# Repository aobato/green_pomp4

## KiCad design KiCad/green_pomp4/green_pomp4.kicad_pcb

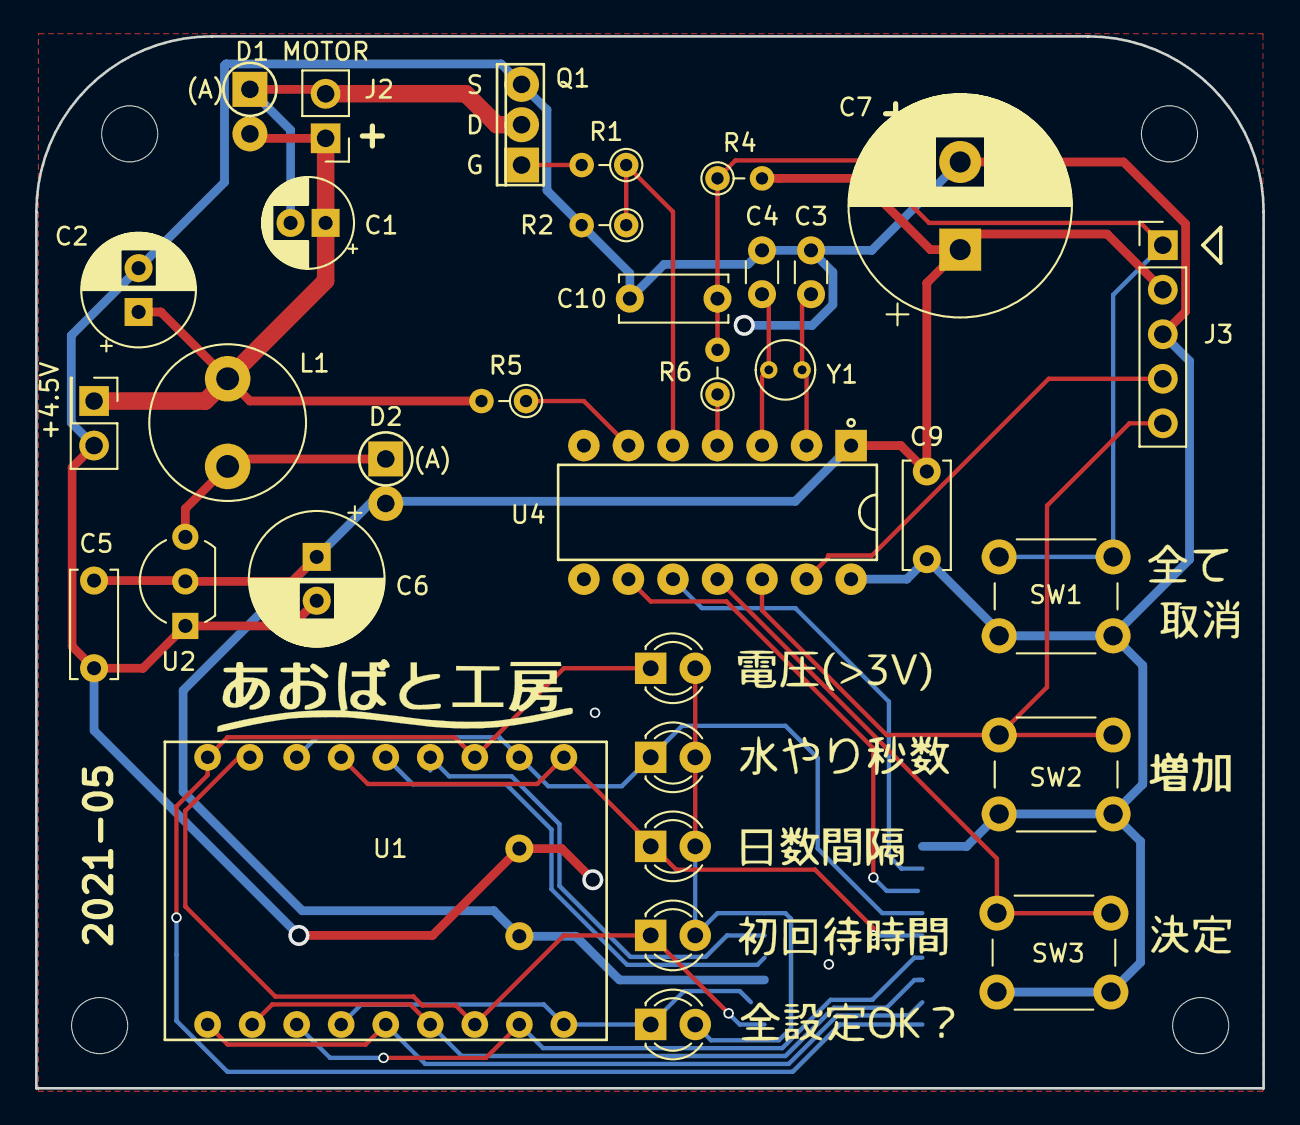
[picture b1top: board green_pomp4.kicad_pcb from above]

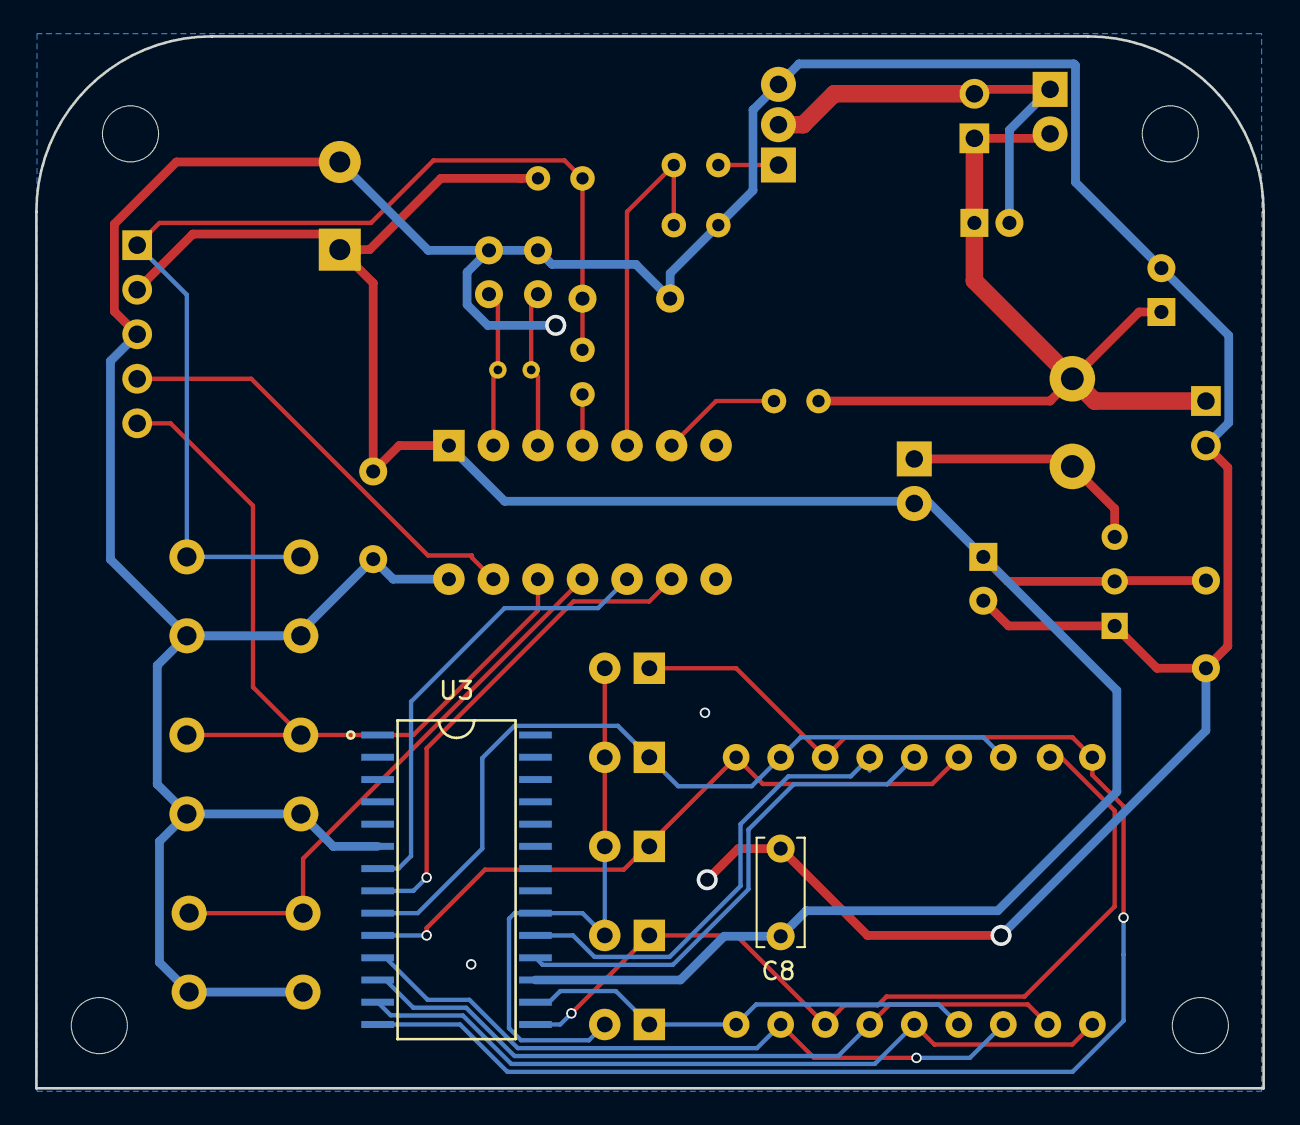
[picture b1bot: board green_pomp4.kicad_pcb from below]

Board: 2 copper layers, 70.0 x 60.0 mm, 39 parts (2 on the bottom side), 28 nets.

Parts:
C1: 22u; CP_Radial_D5.0mm_P2.00mm
C2: 47u; CP_Radial_D6.3mm_P2.50mm
C3, C4: 15p; C_Disc_D3.0mm_W1.6mm_P2.50mm
C5, C8, C9, C10: 0.1u; C_Disc_D6.0mm_W2.5mm_P5.00mm
C6: 100uF; CP_Radial_D7.5mm_P2.50mm
C7: 1000uF; CP_Radial_D12.5mm_P5.00mm
D1, D2: D; 1S4_V
J1: POWER; PinHeader_2x01_P2.54mm_Vertical
J2: MOTOR; PinHeader_1x02_P2.54mm_Vertical
J3: pin_header; PinHeader_1x05_P2.54mm_Vertical
L1: 47uH; L_Radial_D8.7mm_P5.00mm_Fastron_07HCP
LED1: voltage; LED_D3.0mm
LED2: water; LED_D3.0mm
LED3: interval; LED_D3.0mm
LED4: wait; LED_D3.0mm
LED5: start; LED_D3.0mm
M3 hole, M3 hole#2, M3 hole#3, M3 hole#4: MountingHole_3.2mm_M3
Q1: 2SK4017; 2SK4017_Q
R1, R5, R6: 470; R_Axial_DIN0204_L3.6mm_D1.6mm_P2.54mm_Vertical
R2, R4: 10K; R_Axial_DIN0204_L3.6mm_D1.6mm_P2.54mm_Vertical
SW1: reset; SW_PUSH_6mm
SW2: enter; SW_PUSH_6mm
SW3: next; SW_PUSH_6mm
U1: HDSP-K123
U2: HT7750A; TO-92L_Inline_Wide
U3: TM1640; DSPIC30F2010-20I_SO
U4: PIC16F18323-I/P; PIC16F1503-I_P
Y1: 32.768KHz; Crystal_Round_D3.0mm_Vertical

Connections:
+5V: C5.2, C6.1, C7.1, C8.2, C9.2, D2.2, J3.2, R4.2, U2.2, U3.17, U4.1
+BATT: C1.1, C2.1, D1.2, J1.1, J2.1, L1.1, R5.2
GND: C2.2, C3.2, C4.2, C5.1, C6.2, C7.2, C8.1, C9.1, C10.2, J1.2, J3.3, Q1.3, R2.2, SW1.2, SW2.2, SW3.2, U2.1, U3.6, U4.14
unnamed: C1.2, D1.1, J2.2, Q1.2
unnamed: C3.1, U4.2, Y1.1
unnamed: C4.1, U4.3, Y1.2
unnamed: C10.1, J3.1, R4.1, R6.2, SW1.1
unnamed: D2.1, L1.2, U2.3
unnamed: J3.4, U4.13
unnamed: J3.5, SW2.1, U4.12
unnamed: LED1.1, U1.12, U1.18, U3.14
unnamed: LED1.2, LED2.2, LED3.2, LED4.2, LED5.2, U3.20
unnamed: LED2.1, U1.11, U1.16, U3.9
unnamed: LED3.1, U1.10, U1.15, U3.10
unnamed: LED4.1, U1.7, U1.17, U3.15
unnamed: LED5.1, U1.4, U1.9, U3.16
unnamed: Q1.1, R1.2
unnamed: R1.1, R2.1, U4.5
unnamed: R5.1, U4.6
unnamed: R6.1, U4.4
unnamed: SW3.1, U4.11
unnamed: U1.1, U1.5, U3.13
unnamed: U1.2, U1.6, U3.12
unnamed: U1.3, U1.8, U3.11
unnamed: U1.13, U3.19
unnamed: U1.14, U3.18
unnamed: U3.7, U4.10
unnamed: U3.8, U4.9

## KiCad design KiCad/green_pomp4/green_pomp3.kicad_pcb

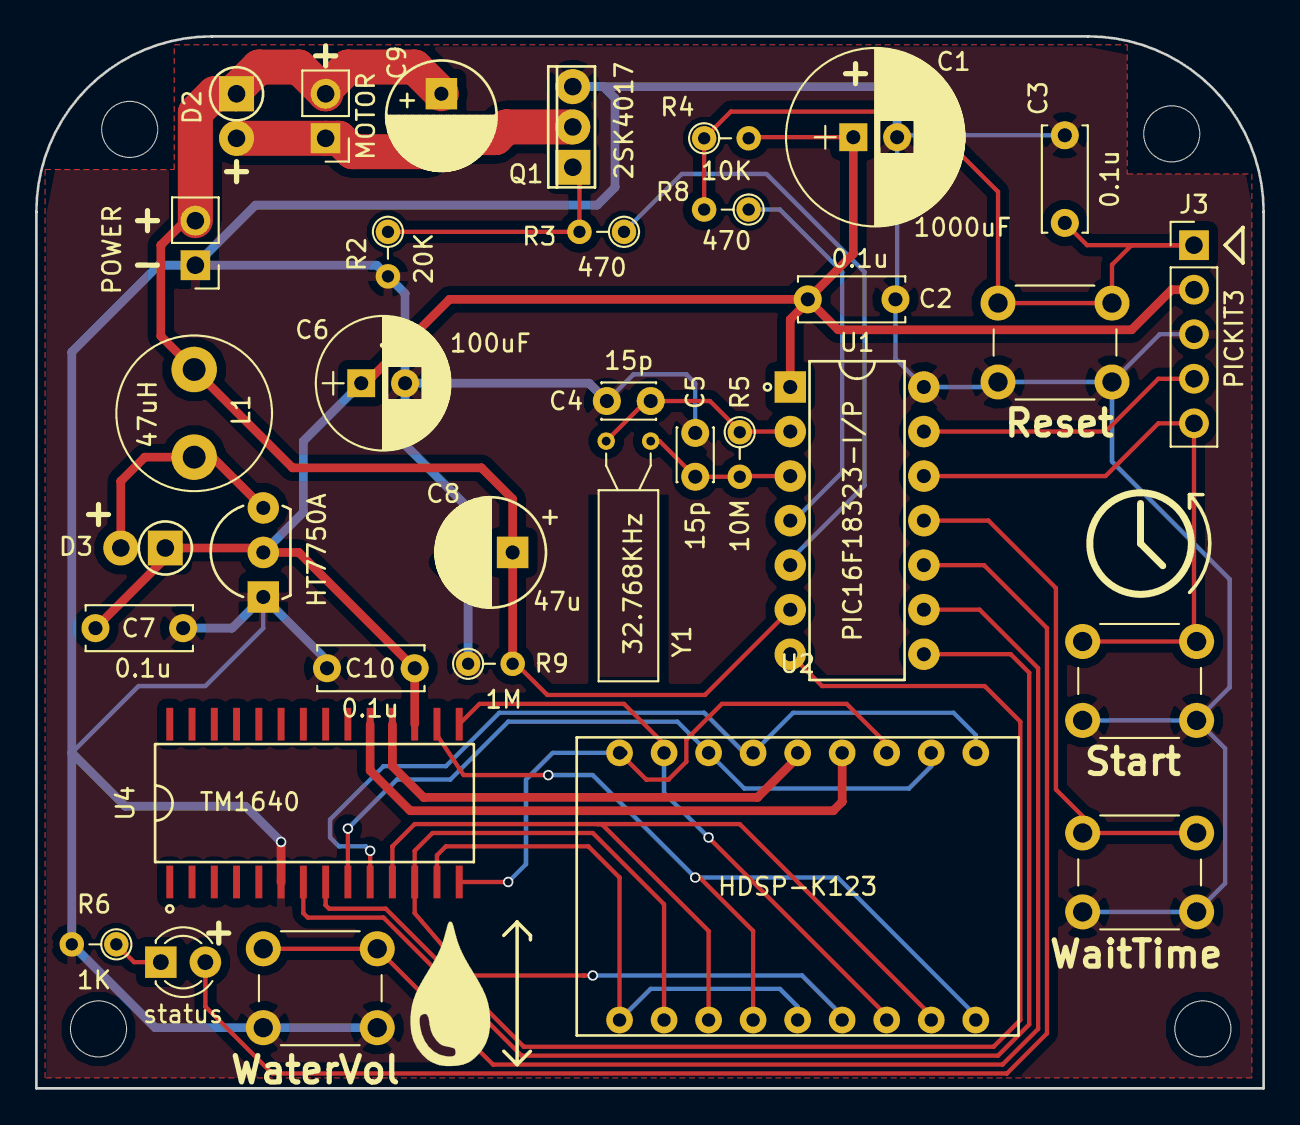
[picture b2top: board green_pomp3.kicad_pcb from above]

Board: 2 copper layers, 70.0 x 60.0 mm, 39 parts (0 on the bottom side), 29 nets.

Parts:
C1: 1000uF; CP_Radial_D10.0mm_P2.50mm
C2, C3, C7, C10: 0.1u; C_Disc_D6.0mm_W2.5mm_P5.00mm
C4, C5: 15p; C_Disc_D3.0mm_W2.0mm_P2.50mm
C6: 100uF; CP_Radial_D7.5mm_P2.50mm
C8: 47u; 25PK220MEFC6.3X11
C9: 22u; 25PK220MEFC6.3X11
D2, D3: D; 1S4_V
G1: LOGO; LOGO4
J1: POWER; Pin_Header_Straight_1x02_Pitch2.54mm
J2: MOTOR; Pin_Header_Straight_1x02_Pitch2.54mm
J3: PICKIT3; Pin_Header_Straight_1x05_Pitch2.54mm
L1: 47uH; L_Radial_D8.7mm_P5.00mm_Fastron_07HCP
LED1: status; LED_D3.0mm
Q1: 2SK4017; 2SK4017_Q
R2: 20K; R_Axial_DIN0204_L3.6mm_D1.6mm_P2.54mm_Vertical
R3, R8: 470; R_Axial_DIN0204_L3.6mm_D1.6mm_P2.54mm_Vertical
R4: 10K; R_Axial_DIN0204_L3.6mm_D1.6mm_P2.54mm_Vertical
R5: 10M; R_Axial_DIN0204_L3.6mm_D1.6mm_P2.54mm_Vertical
R6: 1K; R_Axial_DIN0204_L3.6mm_D1.6mm_P2.54mm_Vertical
R9: 1M; R_Axial_DIN0204_L3.6mm_D1.6mm_P2.54mm_Vertical
REF1, REF2, REF3, REF4: MountingHole_3.2mm_M3
SW1: WaitTime; SW_PUSH_6mm
SW2: WaterVol; SW_PUSH_6mm
SW4: Reset; SW_PUSH_6mm
SW5: Start; SW_PUSH_6mm
U1: PIC16F18323-I/P; PIC16F1503-I_P
U2: HDSP-K123
U3: HT7750A; 2N3904BU
U4: TM1640; DSPIC30F2010-20I_SO
Y1: 32.768KHz; Crystal_AT310_d3.0mm_l10.0mm_Horizontal

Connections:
unnamed: C8.1, C9.1, D2.1, J1.2, J2.2, L1.1, R9.2, U1.6
unnamed: C1.2, C2.1, C3.2, C4.2, C5.2, C6.2, C7.1, C8.2, C10.2, J1.1, J3.3, Q1.3, R2.2, R6.2, R9.1, SW1.2, SW2.2, SW4.2, SW5.2, U1.14, U3.1, U4.6
unnamed: C1.1, C2.2, C6.1, C7.2, C10.1, D3.1, J3.2, R4.2, U1.1, U3.2, U4.17
unnamed: C3.1, J3.1, R4.1, R8.2, SW4.1
unnamed: C4.1, R5.1, U1.2, Y1.1
unnamed: C5.1, R5.2, U1.3, Y1.2
unnamed: C9.2, D2.2, J2.1, Q1.2
unnamed: D3.2, L1.2, U3.3
unnamed: J3.4, U1.13
unnamed: J3.5, SW5.1, U1.12
unnamed: LED1.1, R6.1
unnamed: LED1.2, U1.10
unnamed: Q1.1, R2.1, R3.2
unnamed: R3.1, U1.5
unnamed: R8.1, U1.4
unnamed: SW1.1, U1.11
unnamed: SW2.1, U1.9
unnamed: U1.7, U4.8
unnamed: U1.8, U4.7
unnamed: U2.1, U2.5, U4.13
unnamed: U2.2, U2.6, U4.12
unnamed: U2.3, U2.8, U4.11
unnamed: U2.4, U2.9, U4.16
unnamed: U2.10, U2.15, U4.10
unnamed: U2.11, U2.16, U4.9
unnamed: U2.12, U2.18, U4.14
unnamed: U2.13, U4.19
unnamed: U2.14, U4.18
unnamed: U2.7, U2.17, U4.15

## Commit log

2021-12-18 最初の移行
    とりあえずローカルからKicadとMPLABを全部移行
2021-12-18 説明書をついか
    説明書をついか
2021-12-18 部品表を追加
    部品表を追加
